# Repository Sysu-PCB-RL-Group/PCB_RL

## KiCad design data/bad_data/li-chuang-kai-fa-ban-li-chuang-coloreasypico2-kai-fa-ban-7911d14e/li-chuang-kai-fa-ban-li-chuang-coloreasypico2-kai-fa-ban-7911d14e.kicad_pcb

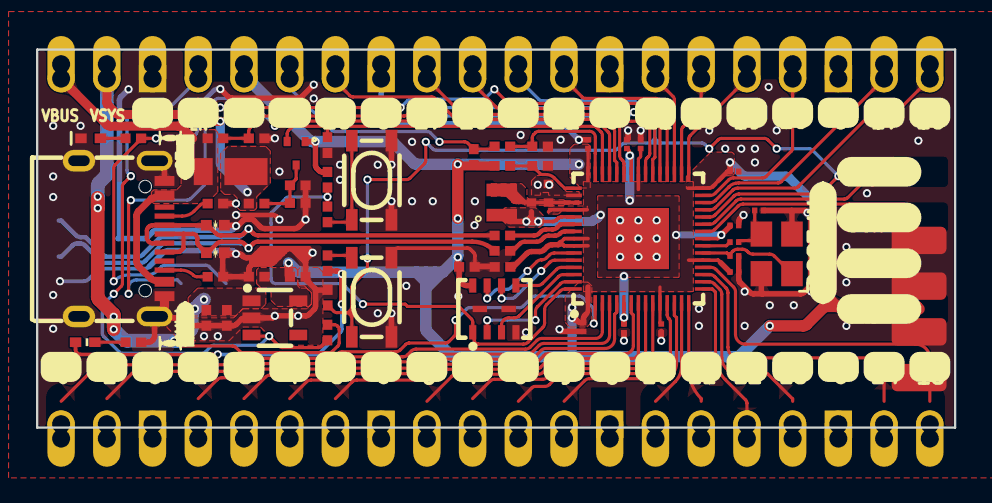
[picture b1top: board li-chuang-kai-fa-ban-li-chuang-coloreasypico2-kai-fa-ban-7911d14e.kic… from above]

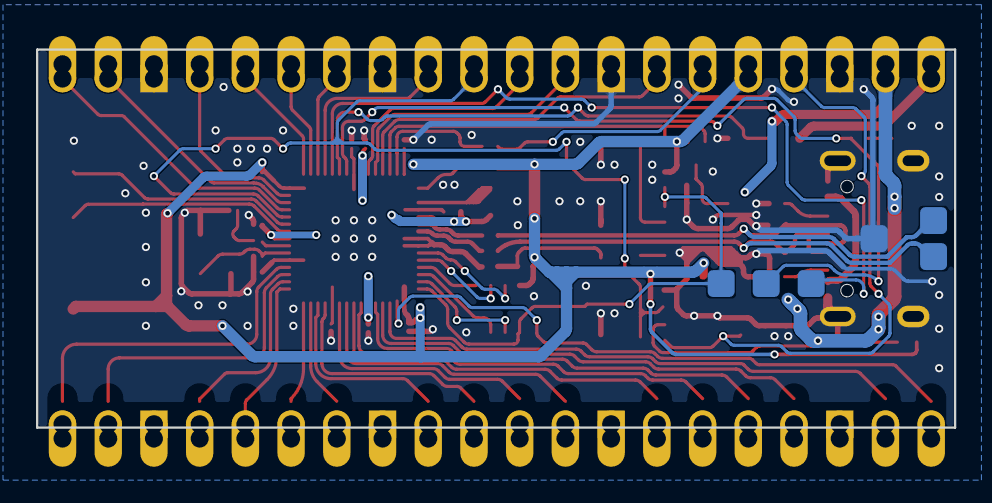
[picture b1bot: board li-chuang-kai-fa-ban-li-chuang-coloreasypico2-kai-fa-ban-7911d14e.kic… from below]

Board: 2 copper layers, 51.0 x 21.0 mm, 65 parts (6 on the bottom side), 63 nets.

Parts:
BOOT1: KEY-SMD_4P-L4.2-W3.2-P2.20-LS5.1-TL
C1, C3: C0402
C2, C4, C7, C8, C10, C11, C12, C13, C21, C24: R0402
C5, C6, C9, C14, C15, C16, C17, C18, C19, C22, C23: R0201
D1: POWERDI-123_L2.8-W1.8-LS3.7-RD
D2, D3: D0402-BI
H1: HDR-TH_4P-P2.54-V-M-1
J1, J2: 半孔-孔-20P-2.54-1.27-无丝印
L2: IND-SMD_L2.0-W1.6_AOTA-B201610S3R3-101-T
LED1: LED0402-RD_GREEN
PWR_LED: LED0402-RD
Q1: SOT-523-3_L1.6-W0.8-P1.00-LS1.6-BR
R1, R2, R3, R4, R5, R6, R7, R8, R9, R10, R11, R12, R13, R14, R15, R16, R17, R19: R0402
R18: R0201
SW1: KEY-SMD_4P-L4.2-W3.2-P2.20-LS5.1-TL
TP1, TP2, TP3, TP4, TP5, TP6: TESTPOINT-TH_BD3.2
U1: QFN-60_L7.0-W7.0-P0.40-TL-EP3.4
U3: SOT-23-5_L3.0-W1.7-P0.95-LS2.8-BR
U4: USON-8_L4.0-W3.0-P0.80-BL_WINBOND_UU
USB1: USB-C-SMD_TYPE-C-6PIN-2MD-073
X1: CRYSTAL-SMD_4P-L3.2-W2.5-BL

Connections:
1V1: C1.2, C9.1, C16.2, C18.1, L2.2, U1.6, U1.23, U1.39, U1.50
3V3: C2.1, C3.1, C5.2, C6.1, C10.2, C11.2, C14.1, C15.2, C17.1, C19.1, C24.2, H1.4, J2.5, PWR_LED.2, Q1.1, R7.2, R9.1, R13.2, R19.2, U1.1, U1.11, U1.20, U1.30, U1.38, U1.45, U1.49, U1.53, U1.54, U3.5, U4.8
3V3_EN: J2.4, R11.2, U3.3
$1N7955: C23.1, R18.2, X1.3
$1N8040: C21.2, Q1.3, R15.1, R16.2
$1N8088: R2.1, USB1.4
$1N8089: R8.1, USB1.10
$1N8094: LED1.2, R1.2
$1N15224: L2.1, U1.48
$1N16315: C4.1, R7.1, U1.46
$1N16648: C8.1, R10.1, U1.44
$1N24312: BOOT1.1, BOOT1.2, R14.1
$1N32447: PWR_LED.1, R12.1
$1N32723: R9.2, SW1.2
ADC_VREF: J2.6, R10.2, R19.1
GND: BOOT1.3, BOOT1.4, C1.1, C2.2, C3.2, C4.2, C5.1, C6.2, C7.1, C8.2, C9.2, C10.1, C11.1, C12.1, C13.1, C14.2, C15.1, C16.1, C17.2, C18.2, C19.2, C21.1, C22.1, C23.2, C24.1, D2.1, D3.1, H1.3, J1.3, J1.8, J1.13, J1.18, J2.3, J2.8, J2.13, J2.18, LED1.1, R2.2, R6.1, R8.2, R12.2, R16.1, R17.1, SW1.3, SW1.4, TP1.1, U1.47, U1.61, U3.2, U4.4, U4.9, U4.10, USB1.1, USB1.12, USB1.13, USB1.14, X1.2, X1.4
GPIO0: J1.1, U1.2
GPIO1: J1.2, U1.3
GPIO2: J1.4, U1.4
GPIO3: J1.5, U1.5
GPIO4: J1.6, U1.7
GPIO5: J1.7, U1.8
GPIO6: J1.9, U1.9
GPIO7: J1.10, U1.10
GPIO8: J1.11, U1.12
GPIO9: J1.12, U1.13
GPIO10: J1.14, U1.14
GPIO11: J1.15, U1.15
GPIO12: J1.16, U1.16
GPIO13: J1.17, U1.17
GPIO14: J1.19, U1.18
GPIO15: J1.20, U1.19
GPIO16: J2.20, U1.27
GPIO17: J2.19, U1.28
GPIO18: J2.17, U1.29
GPIO19: J2.16, U1.31
GPIO20: J2.15, U1.32
GPIO21: J2.14, U1.33
GPIO22: J2.12, U1.34
GPIO23: TP4.1, U1.35
GPIO24: R3.1, R6.2, U1.36
GPIO25: R1.1, TP5.1, U1.37
GPIO26/ADC0: J2.10, U1.40
GPIO27/ADC1: J2.9, U1.41
GPIO28/ADC2: J2.7, U1.42
GPIO29/ADC3: Q1.2, R17.2, U1.43
QSPI_SCLK: U1.56, U4.6
QSPI_SD0: U1.57, U4.5
QSPI_SD1: U1.59, U4.2
QSPI_SD2: U1.58, U4.3
QSPI_SD3: U1.55, U4.7
QSPI_SS: R13.1, R14.2, TP6.1, U1.60, U4.1
RUN: C7.2, J2.11, SW1.1, U1.26
SWCLK: H1.2, U1.24
SWD: H1.1, U1.25
USB2_D+: D3.2, R5.1, TP3.1, USB1.6, USB1.8
USB2_D-: D2.2, R4.1, TP2.1, USB1.5, USB1.7
USB_D+: R5.2, U1.52
USB_D-: R4.2, U1.51
VBUS: D1.2, J2.1, R3.2, USB1.2, USB1.11
VSYS: C12.2, C13.2, D1.1, J2.2, R11.1, R15.2, U3.1
XIN: C22.2, U1.21, X1.1
XOUT: R18.1, U1.22

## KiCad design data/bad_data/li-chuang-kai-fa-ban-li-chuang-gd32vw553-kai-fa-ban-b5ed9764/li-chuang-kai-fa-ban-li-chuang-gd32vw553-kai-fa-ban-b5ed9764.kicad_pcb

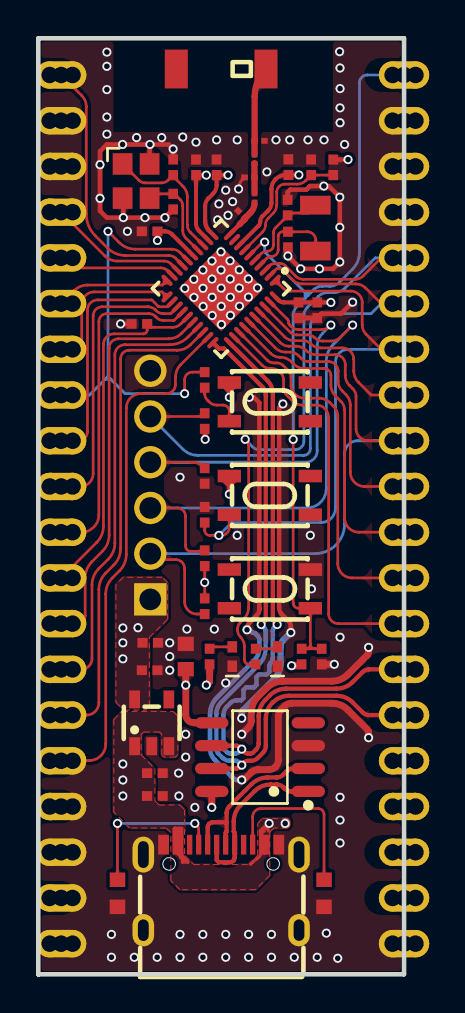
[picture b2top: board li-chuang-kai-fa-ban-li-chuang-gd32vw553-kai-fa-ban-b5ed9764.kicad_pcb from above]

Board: 4 copper layers, 20.3 x 52.0 mm, 50 parts (0 on the bottom side), 46 nets.

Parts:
C1, C2, C17, C18, C21, C28, C29, C30, C31, C45, C46, C47, C48, C49, C53, C54: r0402
C7: C0603
C37, C55, C57: C0201
H1: hdr-th_6p-p2.54-v-m-1
J3, J4: 半孔-孔-20p-2.54-1.27-无丝印
L4: ant-smd_l5.2-w2.0
L6: L0201
LED1: LED0402-RD_GREEN
PWR1: led0402-rd
R1, R2, R3, R4, R9, R13: R0402
R7, R8: R0603
R26, R27, R28, R29, R30: r0402
R31: R0201
SW1, SW2, SW3: SW-SMD_4P-L4.2-W3.3-P2.15-LS5.1
U1: qfn40
U2: SOP-8_L4.9-W3.9-P1.27-LS6.0-BL
U6: sot-23-5_l3.0-w1.7-p0.95-ls2.8-br
USB1: USB-C-SMD_TYPE-C-6PIN-2MD-073
X1: crystal-smd_4p-l2.5-w2.0-bl
X3: osc-smd_l3.2-w1.5

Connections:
3V3: C7.2, C21.1, C29.2, C30.2, C31.2, C45.2, C49.2, C53.2, C54.2, H1.1, J3.4, J3.5, J4.4, R1.2, R2.2, R13.2, R27.1, R28.1, R29.1, SW1.1, SW2.1, U1.8, U1.11, U1.12, U1.15, U1.40, U2.5, U2.8, U6.5
$1N2903: R8.1, USB1.10
$1N2915: R7.1, USB1.4
$1N28047: PWR1.2, R13.1
$1N28050: LED1.2, R26.1
$1N31252: R9.2, SW2.3
$1N47923: C37.2, L4.1, R31.2
$1N51376: C57.2, L6.1, R31.1
+5V: C28.2, C46.2, J3.2, J3.3, J4.2, U6.1, U6.3, USB1.2, USB1.11
GND: C1.1, C2.1, C7.1, C17.1, C18.2, C21.2, C28.1, C29.1, C30.1, C31.1, C37.1, C45.1, C46.1, C47.2, C48.2, C49.1, C53.1, C54.1, C55.1, C57.1, H1.6, J3.1, J3.17, J3.18, J3.19, J4.1, J4.3, J4.18, J4.19, LED1.1, PWR1.1, R3.1, R4.2, R7.2, R8.2, R30.1, SW3.3, U1.41, U2.3, U6.2, USB1.1, USB1.12, USB1.13, USB1.14, X1.2, X1.4
NRST: C2.2, J3.20, R1.1, SW3.1, U1.6
OSC32_IN: C48.1, U1.4, X3.1
OSC32_OUT: C47.1, U1.5, X3.2
PA0_WKUP0: J4.13, R9.1, U1.16
PA1: J4.20, U1.17
PA2: J4.17, U1.18
PA3: J4.16, U1.19
PA4: J4.15, U1.20
PA5: J4.14, U1.21
PA6: J4.12, U1.22
PA7: J4.11, U1.23
PA9: J3.8, U1.32
PA10: J3.9, U1.33
PA11: J3.10, U1.34
PA12: J3.11, U1.35
PA15: H1.5, J3.15, R28.2, U1.2
PB0: J4.10, U1.24
PB1_BOOT1: J4.9, R3.2, U1.25
PB2: J4.8, U1.26
PB3: H1.2, J3.12, R29.2, U1.36
PB4: J3.13, U1.37
PB11: J4.7, U1.27
PB12: J4.6, U1.28
PB13: J4.5, U1.29
PC8_BOOT0: J3.14, R4.1, SW1.3, U1.1
PC13: J3.16, R26.2, U1.3
PU: C1.2, R2.1, U1.7
RF: C55.2, L6.2, U1.10
SWCLK: H1.4, R30.2, U1.39
SWDIO: H1.3, R27.2, U1.38
USART0_RX: J3.7, U1.31, U2.6
USART0_TX: J3.6, U1.30, U2.7
USB_D+: U2.1, USB1.6, USB1.8
USB_D-: U2.2, USB1.5, USB1.7
XTAL_IN: C17.2, U1.13, X1.1
XTAL_OUT: C18.1, U1.14, X1.3

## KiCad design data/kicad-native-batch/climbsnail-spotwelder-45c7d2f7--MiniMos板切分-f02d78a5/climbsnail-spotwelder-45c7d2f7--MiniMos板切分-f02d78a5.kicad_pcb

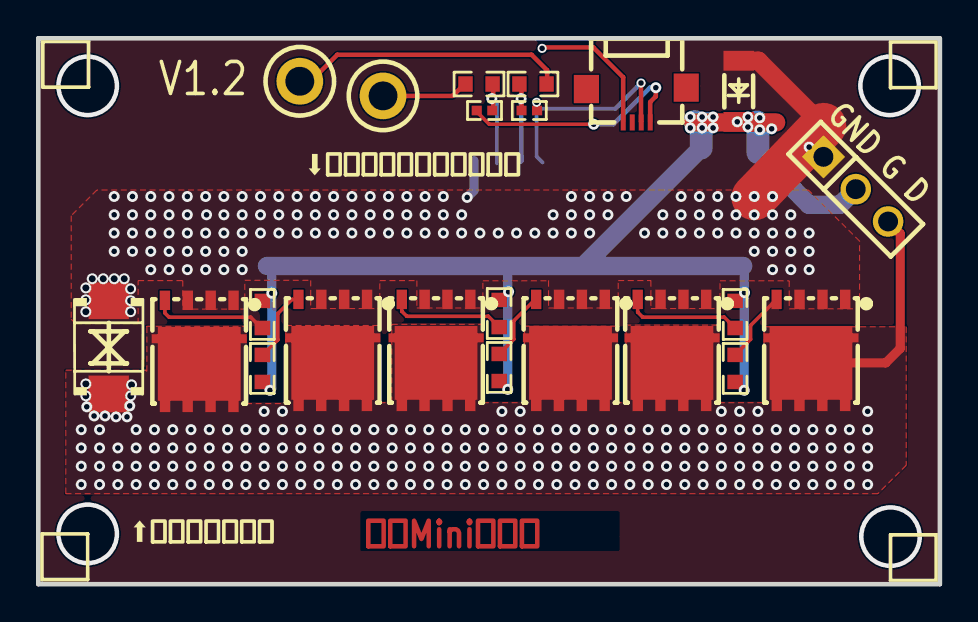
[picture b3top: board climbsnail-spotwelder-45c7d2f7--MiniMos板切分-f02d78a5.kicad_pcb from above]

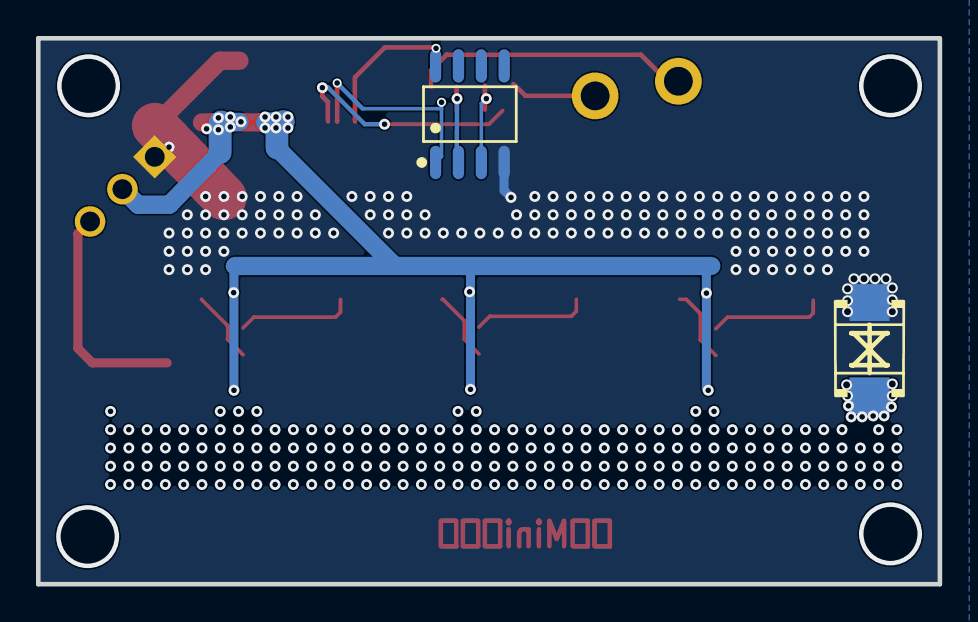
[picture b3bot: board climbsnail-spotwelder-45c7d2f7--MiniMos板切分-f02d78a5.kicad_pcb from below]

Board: 2 copper layers, 50.1 x 30.3 mm, 24 parts (2 on the bottom side), 16 nets.

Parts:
CN1, CN2: TH_BD3.2-D2.0
D4, D5: SMB_L4.6-W3.6-LS5.3-BI
D6: LL-34_L3.5-W1.5-RD
FPC2: FPC-SMD_4P-P0.50_XKB_X05A12H04G
R18, R19, R20, R21, R22, R23, R31, R33: R0603
R28, R32: R0402
U4, U5, U6, U7, U8, U9: DFN-8_L5.8-W5.1-P1.27-LS5.9-BL
U12: SOP-8_L4.9-W3.9-P1.27-LS6.0-BL
U15: HDR-TH_3P-P2.54-V-M

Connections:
$1N69310: R18.2, U4.4
$1N69428: R19.2, U5.4
$1N69546: R20.2, U6.4
$1N69664: R21.2, U7.4
$1N69782: R22.2, U8.4
$1N73187: R23.2, U9.4
$1N135994: R32.1, R33.2, U12.3
$1N136281: R28.2, R31.1, U12.2
$1N157330: CN1.1, R31.2
$1N158078: CN2.1, R33.1
AGND: FPC2.1, R32.2
A_3V3: FPC2.4, U12.8
CUR_VOL: FPC2.2, R28.1, U12.1
GND: D4.2, D5.2, D6.2, U4.1, U4.2, U4.3, U5.1, U5.2, U5.3, U6.1, U6.2, U6.3, U7.1, U7.2, U7.3, U8.1, U8.2, U8.3, U9.1, U9.2, U9.3, U12.4, U15.1
MOS_D2: D4.1, D5.1, U4.5, U4.6, U4.7, U4.8, U4.9, U5.5, U5.6, U5.7, U5.8, U5.9, U6.5, U6.6, U6.7, U6.8, U6.9, U7.5, U7.6, U7.7, U7.8, U7.9, U8.5, U8.6, U8.7, U8.8, U8.9, U9.5, U9.6, U9.7, U9.8, U9.9, U15.3
MOS_G2: D6.1, R18.1, R19.1, R20.1, R21.1, R22.1, R23.1, U15.2

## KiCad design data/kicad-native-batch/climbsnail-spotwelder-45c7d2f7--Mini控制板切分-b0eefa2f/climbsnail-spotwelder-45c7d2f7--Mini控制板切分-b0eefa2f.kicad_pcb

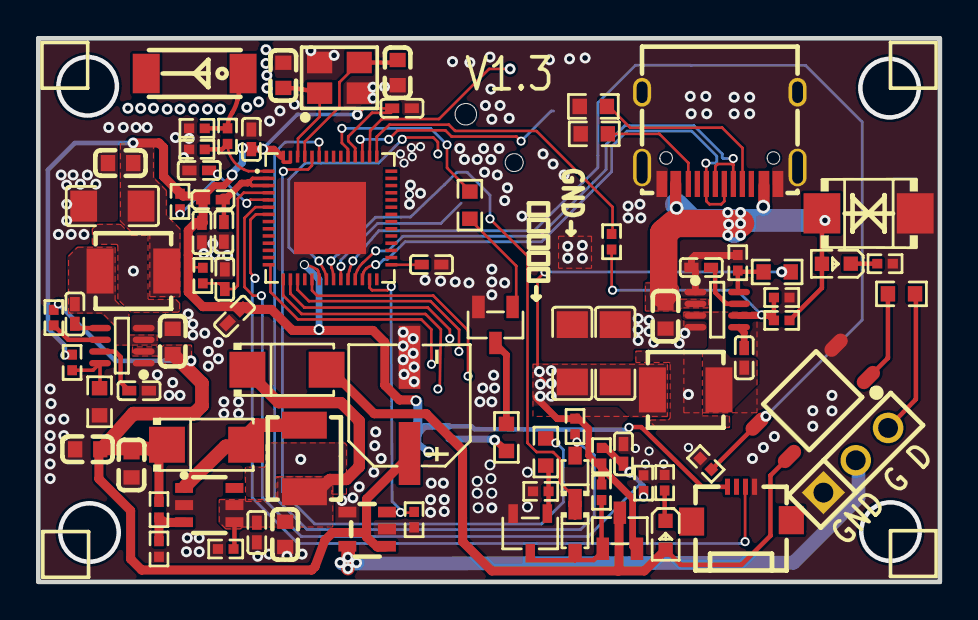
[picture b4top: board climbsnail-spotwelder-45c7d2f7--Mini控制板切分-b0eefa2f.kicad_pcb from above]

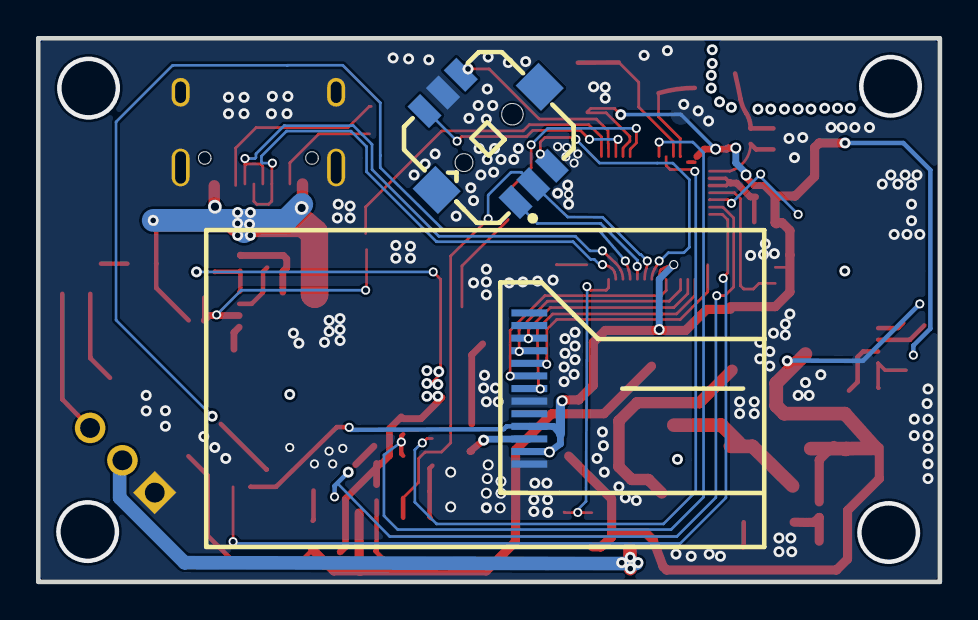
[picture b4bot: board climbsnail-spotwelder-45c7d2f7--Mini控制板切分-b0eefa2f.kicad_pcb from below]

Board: 2 copper layers, 50.1 x 30.2 mm, 84 parts (2 on the bottom side), 59 nets.

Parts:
C1, C3, C4, C6, C7, C10, C11, C12, C13, C14, C20, C21, C24, C26: C0402
C2, C5, C15, C16, C18, C19, C22, C25: C0603
C8, C9, C23: C1206
C17: CAP-SMD_BD6.3-L6.6-W6.6-FD
D1: SMB_L4.6-W3.6-LS5.3-BI
D2, D3: SOD-323_L1.8-W1.3-LS2.5-RD
D7, D8: SMA_L4.3-W2.6-LS5.2-RD
FPC1: FPC-SMD_4P-P0.50_XKB_X05A12H04G
L1: ANT2051
L2: L0402
L3, L5: IND-SMD_L4.2-W4.2-C133189
L4: IND-SMD_L4.5-W4.0-1
LED1, LED2: LED0603-RD_BLUE
Q1, Q3: SOT-23-3_L2.9-W1.3-P1.90-LS2.4-BR
Q2: SOT-23-3_L3.0-W1.7-P0.95-LS2.9-BR
R1, R2, R3, R4, R5, R6, R7, R8, R10, R11, R12, R14, R15, R16, R25, R26, R27, R29, R30, R35, R36, R37, R42: R0402
R9, R13, R17, R24, R34, R38, R39, R40: R0603
SW1: SW-SMD_TM-4175-B-X
U1: QFN-56_L7.0-W7.0-P0.40-TL-EP4.0
U2, U11: TSOT-23-8_L2.9-W1.6-P0.65-LS2.8-BR
U3: 1.14TFT焊接式B
U10: SOT-23-6_L2.9-W1.6-P0.95-LS2.8-BR
U13: SOT-23-5_L2.9-W1.6-P0.95-LS2.8-BR
U14: SOP-4_L4.4-W3.6-P2.54-LS7.0-TL
U16: HDR-TH_3P-P2.54-V-M
USB1: USB-C-SMD_TYPEC-304-BCP16
X1: OSC-SMD_4P-L3.2-W2.5-BL_SIT8008BI

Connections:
3V3: C1.1, C2.2, C3.2, C7.2, C13.1, C23.2, FPC1.1, L2.1, L5.1, R15.2, R26.1, R42.2, U1.20, U1.46, U1.55, U1.56, U3.10, U3.12
$1N280: D7.2, L4.2, U10.1
$1N506: R25.1, R29.2, U10.3
$1N673: C21.2, C22.2, D8.1, L4.1, R30.2, U10.4, U10.5
$1N80208: C10.2, L3.2, U2.3
$1N83125: C10.1, U2.5
$1N83932: C6.1, U2.7
$1N85156: R12.1, R13.1, U2.8
$1N86985: C24.2, L5.2, U11.3
$1N86986: C24.1, U11.5
$1N86989: R27.1, U11.6
$1N86990: C20.1, U11.7
$1N86995: R24.2, R26.2, U11.8
$1N89886: D3.2, Q1.1, Q2.3, R10.2
$1N90159: Q2.1, R9.2, R11.2
$1N102735: C4.2, L2.2, U1.2, U1.3
$1N104052: C14.2, U1.29
$1N111735: R7.2, R8.2, U1.1
$1N112405: L1.1, R6.2, R8.1
$1N115607: LED1.1, R3.1
$1N115916: LED2.1, R5.2
$1N154799: R34.2, U14.1
$1N164036: R14.1, R16.2, R37.2, U2.6
$1N177745: R38.1, USB1.B5
$1N177900: R39.1, USB1.A5
$1N182596: Q3.3, R17.2
$1N183266: R17.1, U3.11
$1N186675: Q3.1, R40.1
+12V: C17.1, C18.2, C19.2, C25.2, D7.1, R25.2, R27.2, U11.2, U13.1
+CAP: C8.2, C9.2, L3.1, Q1.2, R1.2, R2.2, R10.1, R13.2
BOOT: C11.2, R42.1, U1.5
CAP_VOL: C26.2, R2.1, R4.2, U1.6
CUR_VOL: FPC1.3, U1.7
DCDC_PWR_EN: R37.1, U1.43
ENTER: D2.1, D3.1, SW1.2, U1.22
ESP_EN: C12.2, R15.1, U1.4
GND: C1.2, C2.1, C3.1, C4.1, C5.1, C6.2, C7.1, C8.1, C9.1, C11.1, C12.1, C13.2, C14.1, C15.1, C16.2, C17.2, C18.1, C19.1, C20.2, C21.1, C22.1, C23.1, C25.1, C26.1, D1.2, FPC1.4, Q2.2, Q3.2, R3.2, R4.1, R5.1, R6.1, R7.1, R11.1, R12.2, R16.1, R24.1, R29.1, R30.1, R35.1, R36.1, R38.2, R39.2, SW1.5, U1.57, U2.1, U2.4, U3.8, U3.13, U10.2, U11.1, U11.4, U13.2, U13.4, U14.2, U16.1, USB1.13, USB1.14, USB1.15, USB1.16, USB1.A1B12, USB1.B1A12, X1.2, X1.4
IO19: U1.25, USB1.A7, USB1.B7
IO20: U1.26, USB1.A6, USB1.B6
KEY_D: SW1.6, U1.44
KEY_L: SW1.3, U1.21
KEY_R: SW1.4, U1.45
KEY_UP: SW1.1, U1.23
MOS_D: R34.1, U16.3
MOS_G: U13.5, U16.2
MOS_SW: R35.2, U1.27, U13.3
POWER_CHECK: D2.2, R1.1, U1.51
SHORT_EN: R36.2, U1.24, U14.3
START_POWER_EN: R9.1, U1.52
TFT_BL: R40.2, U1.47
TFT_CS: U1.15, U3.7
TFT_DC: U1.14, U3.5
TFT_MOSI: U1.16, U3.3
TFT_RST: U1.19, U3.6
TFT_SCLK: U1.17, U3.4
VBUS: C5.2, D1.1, LED2.2, R14.2, U2.2, USB1.A4B9, USB1.B4A9
WORK+: D8.2, LED1.2, Q1.3, U14.4
XTAL_N: C15.2, U1.53, X1.3
XTAL_P: C16.1, U1.54, X1.1

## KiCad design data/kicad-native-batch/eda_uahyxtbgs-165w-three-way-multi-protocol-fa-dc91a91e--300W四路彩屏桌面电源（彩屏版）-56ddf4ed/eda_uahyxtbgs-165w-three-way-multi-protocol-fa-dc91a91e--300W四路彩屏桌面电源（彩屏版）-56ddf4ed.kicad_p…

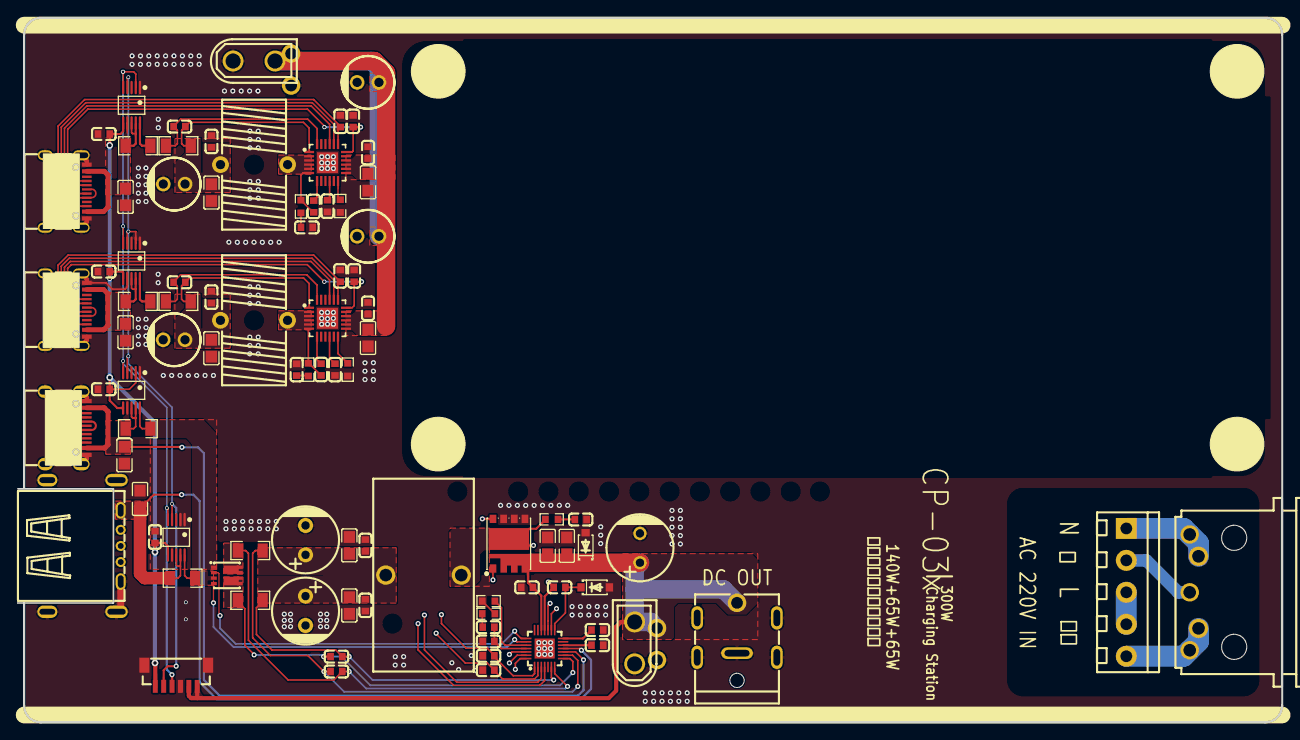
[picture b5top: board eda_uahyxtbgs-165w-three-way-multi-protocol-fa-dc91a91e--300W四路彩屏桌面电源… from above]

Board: 4 copper layers, 150.8 x 84.0 mm, 91 parts (0 on the bottom side), 60 nets.

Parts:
C1, C5, C7, C12, C13, C17, C18, C21, C40, C42, C43: C0603
C2, C32: C0603_4
C3, C8, C9, C15, C16, C19, C20, C22, C23, C25, C34, C36, C37, C39, C41, C44, C47, C48, C49, C50: C0603_1
C4, C6, C10, C11, C14, C24, C26, C33, C35, C38, C45, C46: C0805
CN2: CONN-TH_DB-6-1P4P3
CN3: CONN-TH_XT30UPB-M
CN5: CONN-TH_DB125-3.81-5P-GN-S
EC1: CAP-TH_BD8.0-P3.50-D0.6-FD-2
EC2, EC3: CAP-TH_BD8.0-P3.50-D0.6-FD
EC4, EC5, EC6, EC7: CAP-TH_BD6.3-P2.60-D0.6-FD-1
J1, J3, J4: USB-C-SMD_U263-163N-4GS1735
J2: USB-A-TH_U224-051N-3GRA035
L1: IND-TH_L23.0-W12.0-P9.00-D1.3
L3, L4: IND-TH_L15.5-W7.5-P8.00-D0.8
Q1: DFN-8_L6.0-W5.0-P1.27_AON6938
Q4: DFN-8_L3.0-W3.0-P0.65-LS3.4-BL
R1, R7, R22: R0603
R2, R8, R20, R23: R0603_1
R9, R11, R12, R21, R24, R25, R26, R27: R1206
T1, T2: SOD-123_L2.6-W1.6-LS3.5-RD
U1, U11: QFN-24_L4.0-W4.0-P0.50-TL-EP2.5
U2: QFN-28_L4.0-W4.0-P0.40-TL-EP2.4
U4: CONN-TH_XT30UPB-M
U5: DC-IN-TH_HX-DC007B-2.5
U7, U8, U9, U10: MSOP-10_L3.0-W3.0-P0.50-LS5.0-BL
U12: CONN-SMD_6P-P1.00_X1002WVS-06E-LPSWHF

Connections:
3V3: C47.2, C48.2, C49.2, C50.2, U7.6, U8.6, U9.2, U9.6, U10.6, U12.1
$C2_2: C2.2, R1.2
$C13_2: C13.2, U2.14
$C20_1: C20.1, U1.7
$C22_2: C22.2, R8.1
$C32_2: C32.2, R20.1
$C39_1: C39.1, U11.7
$C44_2: C44.2, R23.1
$Q4_1: Q4.1, R27.2, U9.10
$Q4_3: Q4.3, R26.2, U7.10
$R7_2: R7.2, U1.12
$R22_2: R22.2, U11.12
BST1: C8.1, T1.1, U2.15
CC1: C18.1, J3.A5, U1.18
CC1-2: C43.1, J4.A5, U11.18
CC1_1: C7.1, J1.A5, U2.2
CC2: C17.1, J3.B5, U1.19
CC2-2: C42.1, J4.B5, U11.19
CC2_1: C5.1, J1.B5, U2.1
COMP1: C1.1, C2.1, U2.25
CSN: C25.2, R12.2, R24.1, U1.24, U8.10
CSN2: C37.2, R21.2, R25.1, U10.10, U11.24
CSNA1: C15.2, Q4.5, Q4.6, R11.2, U2.8
CSNC1: C16.1, Q4.7, Q4.8, R9.2, U2.7
CSP: C23.2, C24.2, C25.1, EC5.1, L3.2, R12.1, U1.1
CSP2: C36.2, C37.1, C46.2, EC6.1, L4.2, R21.1, U11.1
CSPA1: C9.2, C10.2, C15.1, C16.2, C33.2, C34.2, EC2.1, EC3.1, L1.2, R9.1, R11.1, U2.6, U2.9
DMA1: J2.2, U2.28
DMC: J3.A7, J3.B7, U1.21
DMC2: J4.A7, J4.B7, U11.21
DMC_1: J1.A7, J1.B7, U2.4
DPA1: J2.4, U2.27
DPC: J3.A6, J3.B6, U1.20
DPC2: J4.A6, J4.B6, U11.20
DPC_1: J1.A6, J1.B6, U2.3
GATEA1: Q4.4, U2.23
GATEC1: Q4.2, U2.22
GND: C1.2, C3.1, C4.1, C5.2, C6.1, C7.2, C9.1, C10.1, C11.1, C12.1, C13.1, C14.1, C17.2, C18.2, C19.1, C21.1, C22.1, C23.1, C24.1, C26.1, C32.1, C33.1, C34.1, C35.1, C36.1, C38.1, C40.1, C41.1, C42.2, C43.2, C44.1, C45.1, C46.1, C47.1, C48.1, C49.1, C50.1, CN3.1, EC1.2, EC2.2, EC3.2, EC4.2, EC5.2, EC6.2, EC7.2, J1.A1, J1.A12, J1.B1, J1.B12, J1.SH1, J2.5, J2.6, J2.7, J2.8, J2.9, J3.A1, J3.A12, J3.B1, J3.B12, J3.SH1, J4.A1, J4.A12, J4.B1, J4.B12, J4.SH1, Q1.3, Q1.4, Q1.5, R1.1, R2.1, R7.1, R22.1, T1.2, T2.2, U1.25, U2.29, U4.1, U5.2, U5.3, U7.1, U7.2, U7.7, U8.1, U8.7, U9.1, U9.7, U10.1, U10.7, U11.25, U12.4, U12.7, U12.8
HGATE1: Q1.1, U2.17
IDA1: J2.3, U2.26
L: CN5.3, CN5.4
LGATE1: Q1.6, U2.16
LIN: CN2.1, CN5.5
N: CN2.3, CN5.1
NTC1: R2.2, U2.24
PGND: CN2.2, CN5.2
SCL: U7.5, U8.5, U9.5, U10.2, U10.5, U12.3
SDA: U7.4, U8.2, U8.4, U9.4, U10.4, U12.2
SW: C20.2, L3.1, R8.2, U1.2, U1.3, U1.4, U1.5, U1.6
SW1: C8.2, L1.1, Q1.7, R20.2, U2.18
SW2: C39.2, L4.1, R23.2, U11.2, U11.3, U11.4, U11.5, U11.6
VBUSA1: C11.2, J2.1, R26.1, U2.11, U7.8, U7.9
VBUSC: C26.2, J3.A4, J3.A9, J3.B4, J3.B9, R24.2, U8.8, U8.9
VBUSC1: C14.2, J1.A4, J1.A9, J1.B4, J1.B9, R27.1, U2.10, U9.8, U9.9
VBUSC2: C38.2, J4.A4, J4.A9, J4.B4, J4.B9, R25.2, U10.8, U10.9
VDD1: C12.2, U2.12
VDRV: C21.2, U1.10
VDRV2: C40.2, U11.10
VIN: C3.2, C4.2, C35.2, EC1.1, Q1.2, T2.1, U2.19, U4.2, U5.1, U12.5, U12.6
VIN2: C6.2, C19.2, C41.2, C45.2, CN3.2, EC4.1, EC7.1, U1.13, U1.14, U1.15, U1.16, U11.13, U11.14, U11.15, U11.16

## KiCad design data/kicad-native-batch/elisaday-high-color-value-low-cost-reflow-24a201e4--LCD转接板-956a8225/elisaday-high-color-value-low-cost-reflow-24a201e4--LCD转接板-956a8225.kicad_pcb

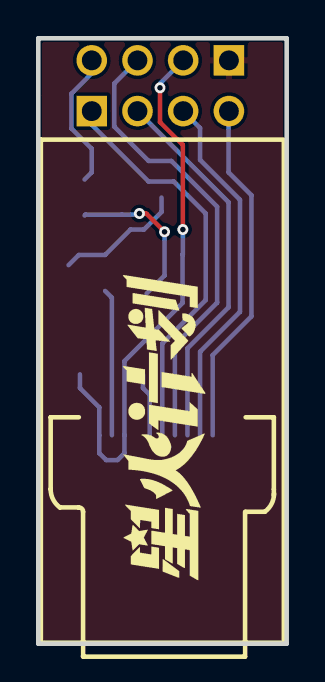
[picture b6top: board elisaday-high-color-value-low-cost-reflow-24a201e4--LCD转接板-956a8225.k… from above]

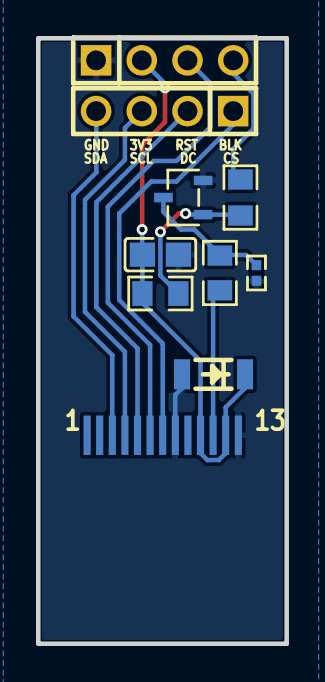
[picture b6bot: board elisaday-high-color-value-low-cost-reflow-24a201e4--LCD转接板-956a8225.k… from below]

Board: 2 copper layers, 13.8 x 33.6 mm, 10 parts (9 on the bottom side), 11 nets.

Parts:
C9: C0805
D3: LL-34_L3.5-W1.5-LS3.5-FD
H2, H3: HDR-TH_4P-P2.54-V-M
Q5: SOT-23-3_L3.0-W1.7-P0.95-LS2.9-BR
R20, R22: R0805
R21: R0805_NEW
R23: R0402
U15: OLED-SMD_ST7735S

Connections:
$6N4490: Q5.1, R20.2, R22.2
$6N4494: Q5.3, R21.1, R23.2
$6N4528: R21.2, U15.11
+3.3V: C9.2, D3.2, H3.2, R22.1, U15.10, U15.12
BLK: H3.4, R20.1
CS: H2.1, U15.7
DC: H2.2, U15.5
GND: C9.1, D3.1, H3.1, Q5.2, R23.1, U15.8, U15.13
RST: H3.3, U15.6
SCL: H2.3, U15.4
SDA: H2.4, U15.3

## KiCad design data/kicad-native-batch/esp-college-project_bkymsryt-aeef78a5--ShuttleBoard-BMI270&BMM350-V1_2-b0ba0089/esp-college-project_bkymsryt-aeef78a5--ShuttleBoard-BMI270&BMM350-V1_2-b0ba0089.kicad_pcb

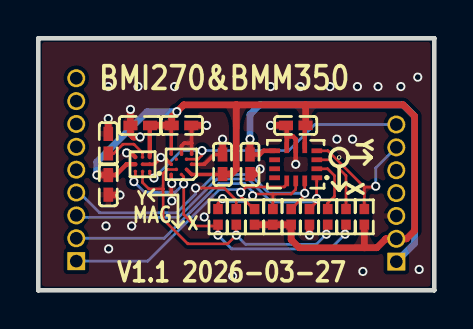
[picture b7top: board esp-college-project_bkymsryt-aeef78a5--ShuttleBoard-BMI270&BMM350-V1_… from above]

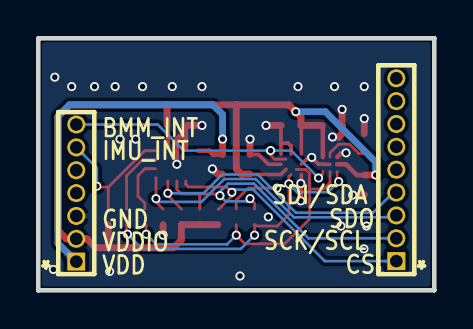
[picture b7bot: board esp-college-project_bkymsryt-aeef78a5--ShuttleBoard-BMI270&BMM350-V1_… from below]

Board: 2 copper layers, 22.0 x 14.0 mm, 21 parts (2 on the bottom side), 14 nets.

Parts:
C1, C2, C3, C4, C5, C6, C7: C0402
H1: HDR-TH_9P-P1.27-V-M
H2: HDR-TH_7P-P1.27-V-M-2
R1, R2, R5, R6, R7, R9, R11: R0402_1
R3, R4: R0402
U1: LGA-14_L3.0-W2.5-P0.50-BR
U2: WLCSP-12_L1.6-W1.6_BMM150
U3: WLCSP-9_L1.3-W1.3-R3-C3-P0.40-TL

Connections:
$1N576: R6.1, U1.3
$1N584: R2.1, U1.2
$1N2196: C2.1, U3.C2
A_SCL: R6.2, R9.2, U2.A3, U3.A3
A_SDA: R2.2, R11.2, U2.B4, U3.A2
BMM_INT: H2.7, U2.D2, U3.A1
CS: H1.1, R7.1, U1.12
GND: C1.1, C2.2, C3.1, C4.1, C5.1, C6.1, C7.1, H2.3, R1.1, U1.6, U1.7, U2.A5, U2.C1, U2.C5, U2.E1, U2.E3, U3.B1, U3.B2, U3.C3
IMU_INT: H2.6, R5.2, U1.4
SCK/SCL: H1.2, R4.2, R9.1, U1.13
SDI/SDA: H1.4, R3.2, R11.1, U1.14
SDO: H1.3, R1.2, U1.1
VDD: C7.2, H2.1, U1.8
VDDIO: C1.2, C3.2, C4.2, C5.2, C6.2, H2.2, R3.1, R4.1, R5.1, R7.2, U1.5, U2.A1, U2.B2, U2.E5, U3.B3, U3.C1
